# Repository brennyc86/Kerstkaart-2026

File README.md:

# Kerstkaart 2026 – Rudolf het rendier

Een printplaat in de vorm van een rendier (96 × 98 mm) met 42 piepkleine NeoPixels. De ATtiny is het **oog**, het knopje is de **neus**,
de overige onderdelen zijn wimpers en wenkbrauw. Op de voorkant staat de kerstboodschap *Zalig Kerstfeest en een gelukkig 2027*.

| Voorkant | Achterkant |
|---|---|
|  |  |

## Ontwerp

| Onderdeel | Type | LCSC |
|---|---|---|
| 42 × LED | SK6805-EC15, 1,5 × 1,5 mm NeoPixel (5 mA, 3,7–5,5 V) | C2890035 |
| Oog | ATtiny1616-MNR, VQFN-20 3×3 mm | C507118 |
| Neus | Omron B3U-1000P, 3 × 2,5 mm tactknopje | C231329 |
| C1 / R1 / R2 | 100 nF / 330 Ω (data) / 4,7 kΩ (UPDI), alle 0603 | C14663 / C23138 / C23162 |

* **Chip als oog:** een witte silkring maakt van de QFN de pupil; C1, R1 en R2 staan rond de ring als wimpers, met een wenkbrauw erboven.
* **Knop als neus:** de B3U zit in de snuit, met de rode neus-LED ernaast; een silkring om beide. Indrukken = volgend lichtprogramma, lang indrukken = helderheid.
* **Geweien identiek:** gewei A is een exacte spiegel van gewei B (elk 5 LED's); de firmware gebruikt `gewei_rang()` zodat alle effecten links en rechts gelijk lopen.
* **LED's recht:** alle LED's staan in 0°/90°/180°/270° t.o.v. de footprint.
* **Batterij (3 × AAA, ≥ 4,5 V):** grote koperpads `+` / `-` op de achterkant (4,6 × 3,8 mm) om draden of een batterijhouder op te solderen. De JST-connector is vervallen.
* **Programmeren, op de achterkant:** rij `GND – UPDI 4k7 – VCC` met UPDI in het midden (via R2), en een aparte pad **`HV: UPDI direct`** die rechtstreeks aan de UPDI-pen hangt voor hoogspanningsprogrammering.
* **Pinnen** (uit het KiCad-symbool): pen 3 GND, 4 VCC, 8 PA7 = knop, 15 PC0 = data, 19 UPDI, 21 = EP (GND).

* **Koper tot de rand:** beide lagen zijn gevuld tot 0,3 mm van de rand (voorkant GND, achterkant VCC), ook smalle randstroken. Losse stukken zijn zwevend koper, puur optisch.
* **GND-via's:** bij elke GND-aansluiting (alle LED's, ATtiny, C1, knop) zit een via vlak ernaast. De onderlaag is VCC-vlak, dus elke via heeft daar een klein eilandje met vrije ruimte eromheen.

## Kleurkeuze (1 kleur silk)
Zwart soldeermasker, witte silk, ENIG-goud: de LED's lichten het mooist op, de boodschap is goed leesbaar en het goud accentueert de blanke pads (`HV`, `UPDI`, batterijpads, oog en neus).
Alternatief: rood masker + witte silk. Een volledig kleuren-silkscreen is een EasyEDA Pro-functie die ik hier niet kan genereren.

## Bestanden

| Pad | Inhoud |
|---|---|
| `kerstkaart_2026_gerber.zip` | Gerbers + boorbestand (JLCPCB) |
| `productie/BOM_kerstkaart_2026.csv`, `productie/CPL_kerstkaart_2026.csv` | Stuklijst en plaatsingsbestand |
| `kerstkaart2026.kicad_pcb` | KiCad-bord (KiCad 10-formaat, **ongetest**, de Gerbers zijn leidend) |
| `footprints/` | De KiCad-bibliotheekfootprints van alle onderdelen |
| `firmware/kerstkaart2026/` | Arduino-sketch (megaTinyCore + tinyNeoPixel) + `leds.h` |
| `gen.py`, `shape.py`, `ketting.py`, `kunst.py`, `sexp.py` | Generator: silhouet, LED-volgorde, silk-kunst → Gerbers, BOM, CPL, renders, `leds.h` |

## Nog controleren
* **Gerbers/CPL:** ingelezen met `gerbonara` (8 lagen + boorbestand herkend), maar niet in KiCad of in JLC's viewer bekeken. Controleer daar de **rotatie** van LED's, U1, knop en connector (JLC wijkt soms 90°/180° af), en of JLC de SK6805-EC15 en B3U-1000P op voorraad heeft.
* **Mijn eigen controle** (spoor/pad-afstand 0,2 mm, randafstand 0,4 mm, GND en VCC elk één samenhangend vlak) is geen volledige DRC.
* **SK6805-EC15:** pinout uit de datasheet (1 DIN, 2 VDD, 3 DOUT, 4 GND, GND linksboven gezien van boven); de padmaten (0,5 × 0,5 mm op 0,9 mm) komen uit de KiCad EC15-footprint, niet uit de datasheet-afbeelding. Het type is dimmer (5 mA) en heeft minstens 3,7 V nodig: een bijna lege batterij laat de LED's eerder uitvallen dan de chip.
* De 0603-LCSC-nummers zijn niet apart geverifieerd. De 5-LED-geweien laten de binnenste zijtak onverlicht.
* Firmware alleen op syntax gecontroleerd, niet op een echte ATtiny.

## Licentie en bronnen
De footprints in `footprints/` komen uit de KiCad-bibliotheken (CC-BY-SA 4.0 met uitzondering voor het gebruik in ontwerpen). De overige bestanden zijn van Brendan.

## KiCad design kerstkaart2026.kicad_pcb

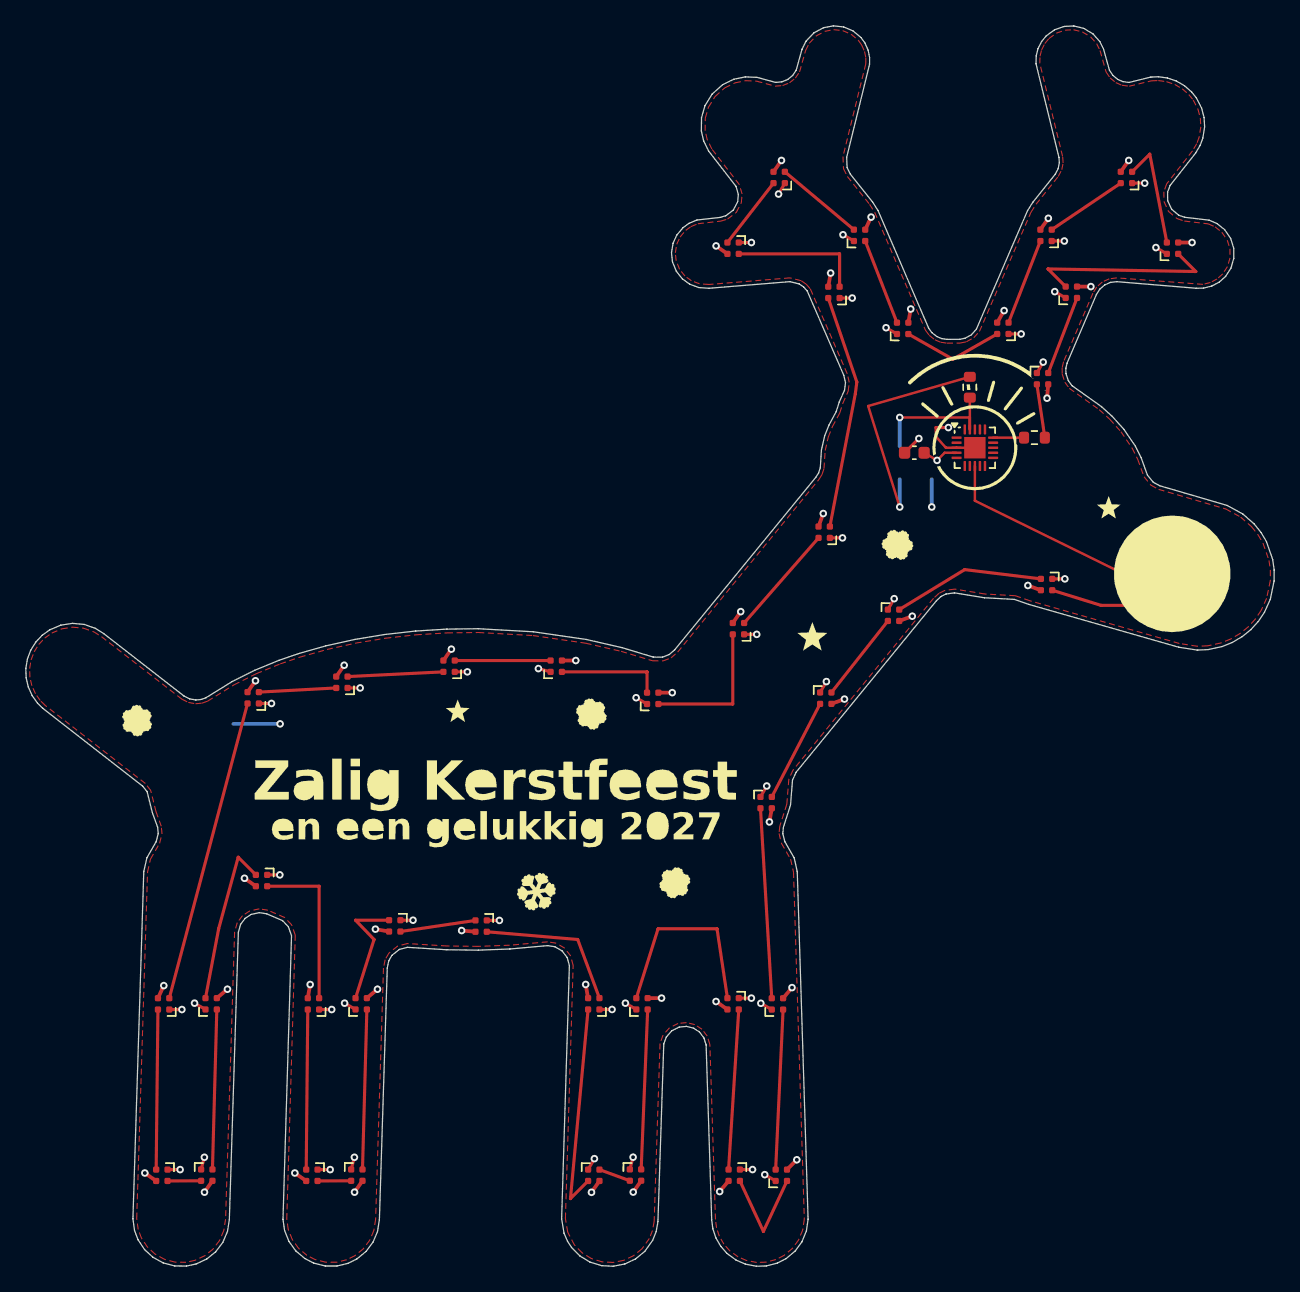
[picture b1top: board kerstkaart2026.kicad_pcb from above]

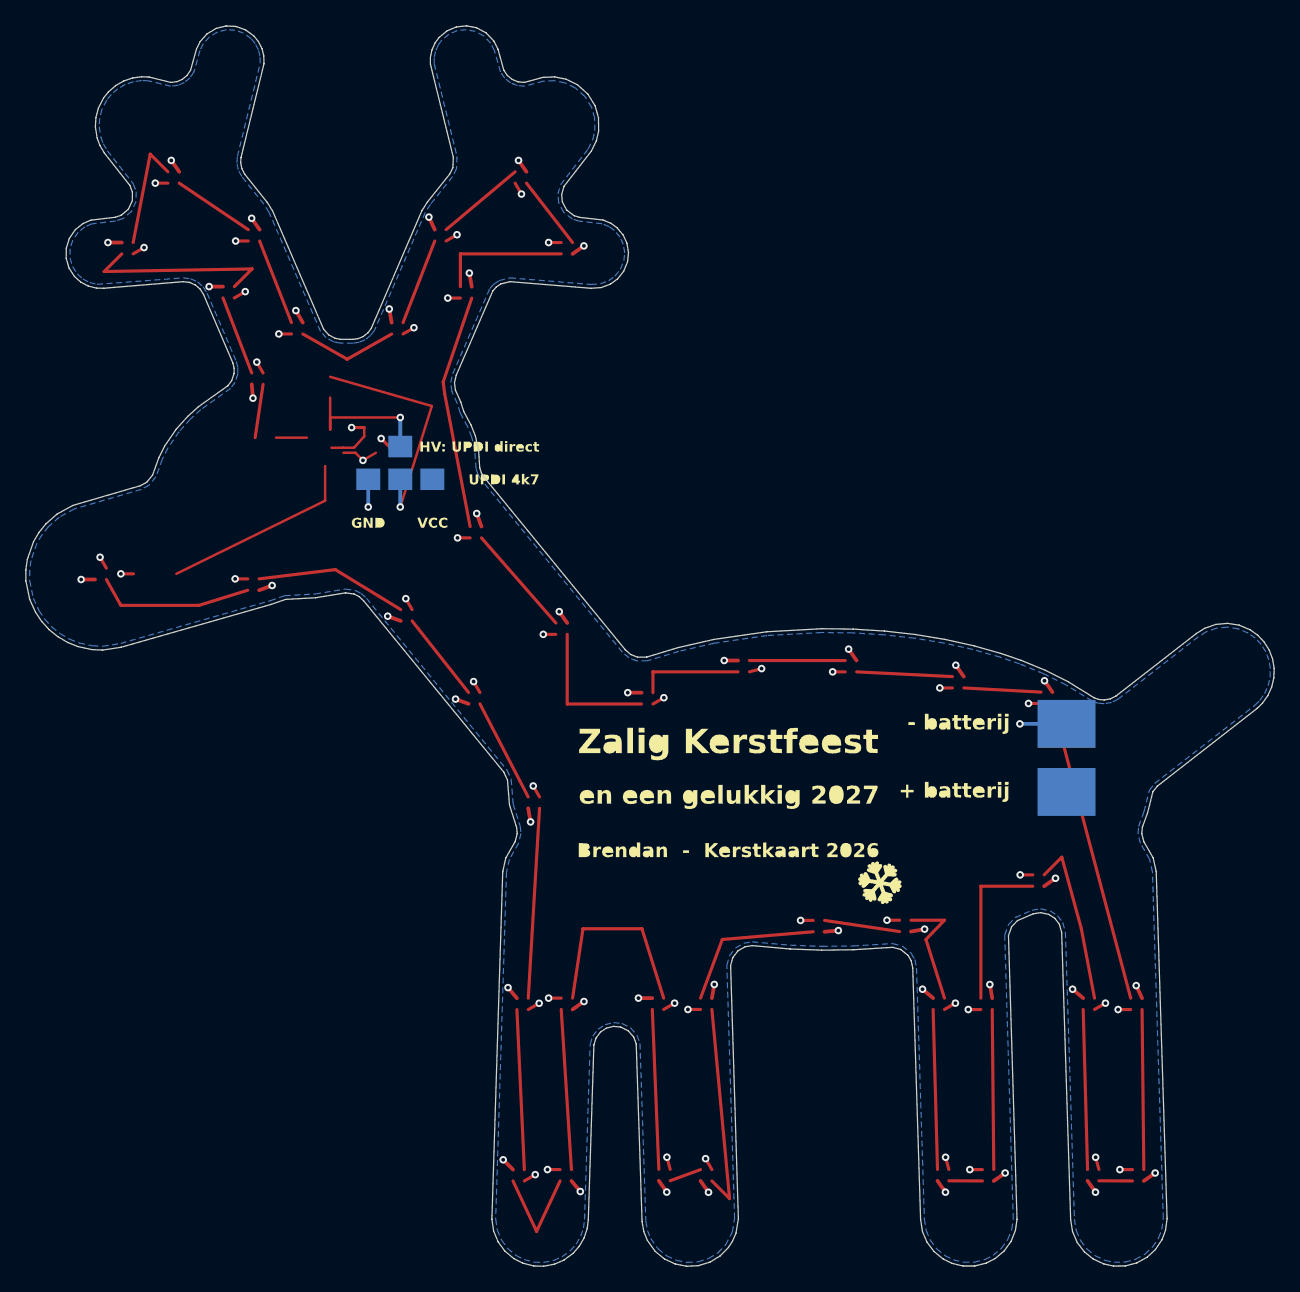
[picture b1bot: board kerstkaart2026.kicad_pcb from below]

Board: 2 copper layers, 99.0 x 98.4 mm, 53 parts (6 on the bottom side), 48 nets.

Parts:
C1: 100nF 0603; C_0603_1608Metric
D1, D2, D3, D4, D5, D6, D7, D8, D9, D10, D11, D12, D13, D14, D15, D16, D17, D18, D19, D20, D21, D22, D23, D24, D25, D26, D27, D28, D29, D30, D31, D32, D33, D34, D35, D36, D37, D38, D39, D40, D41, D42: SK6805-EC15; LED_SK6812_EC15_1.5x1.5mm
R1: 330R 0603; R_0603_1608Metric
R2: 4.7k 0603; R_0603_1608Metric
SW1: B3U-1000P; SW_SPST_B3U-1000P
TP_BT+: Pad_BT+
TP_BT-: Pad_BT-
TP_GND: Pad_GND
TP_HV: Pad_HV
TP_UPDI: Pad_UPDI
TP_VCC: Pad_VCC
U1: ATtiny1616-MNR (VQFN-20); VQFN-20-1EP_3x3mm_P0.4mm_EP1.7x1.7mm

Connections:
BTN: SW1.1, U1.8
D1: D1.3, D2.1
D2: D2.3, D3.1
D3: D3.3, D4.1
D4: D4.3, D5.1
D5: D5.3, D6.1
D6: D6.3, D7.1
D7: D7.3, D8.1
D8: D8.3, D9.1
D9: D9.3, D10.1
D10: D10.3, D11.1
D11: D11.3, D12.1
D12: D12.3, D13.1
D13: D13.3, D14.1
D14: D14.3, D15.1
D15: D15.3, D16.1
D16: D16.3, D17.1
D17: D17.3, D18.1
D18: D18.3, D19.1
D19: D19.3, D20.1
D20: D20.3, D21.1
D21: D21.3, D22.1
D22: D22.3, D23.1
D23: D23.3, D24.1
D24: D24.3, D25.1
D25: D25.3, D26.1
D26: D26.3, D27.1
D27: D27.3, D28.1
D28: D28.3, D29.1
D29: D29.3, D30.1
D30: D30.3, D31.1
D31: D31.3, D32.1
D32: D32.3, D33.1
D33: D33.3, D34.1
D34: D34.3, D35.1
D35: D35.3, D36.1
D36: D36.3, D37.1
D37: D37.3, D38.1
D38: D38.3, D39.1
D39: D39.3, D40.1
D40: D40.3, D41.1
D41: D41.3, D42.1
DATA0: R1.1, U1.15
DATA1: D1.1, R1.2
GND: C1.1, D1.4, D2.4, D3.4, D4.4, D5.4, D6.4, D7.4, D8.4, D9.4, D10.4, D11.4, D12.4, D13.4, D14.4, D15.4, D16.4, D17.4, D18.4, D19.4, D20.4, D21.4, D22.4, D23.4, D24.4, D25.4, D26.4, D27.4, D28.4, D29.4, D30.4, D31.4, D32.4, D33.4, D34.4, D35.4, D36.4, D37.4, D38.4, D39.4, D40.4, D41.4, D42.4, SW1.2, TP_BT-.1, TP_GND.1, U1.3, U1.21
UPDI0: R2.1, TP_HV.1, U1.19
UPDI_R: R2.2, TP_UPDI.1
VCC: C1.2, D1.2, D2.2, D3.2, D4.2, D5.2, D6.2, D7.2, D8.2, D9.2, D10.2, D11.2, D12.2, D13.2, D14.2, D15.2, D16.2, D17.2, D18.2, D19.2, D20.2, D21.2, D22.2, D23.2, D24.2, D25.2, D26.2, D27.2, D28.2, D29.2, D30.2, D31.2, D32.2, D33.2, D34.2, D35.2, D36.2, D37.2, D38.2, D39.2, D40.2, D41.2, D42.2, TP_BT+.1, TP_VCC.1, U1.4

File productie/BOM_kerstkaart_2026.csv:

Comment,Designator,Footprint,LCSC Part #
"ATtiny1616-MNR (VQFN-20)","U1",VQFN-20-1EP_3x3mm_P0.4mm_EP1.7x1.7mm,C507118
"100nF 0603","C1",C_0603_1608Metric,C14663
"330R 0603","R1",R_0603_1608Metric,C23138
"4.7k 0603","R2",R_0603_1608Metric,C23162
"B3U-1000P","SW1",SW_SPST_B3U-1000P,C231329
"SK6805-EC15","D1,D2,D3,D4,D5,D6,D7,D8,D9,D10,D11,D12,D13,D14,D15,D16,D17,D18,D19,D20,D21,D22,D23,D24,D25,D26,D27,D28,D29,D30,D31,D32,D33,D34,D35,D36,D37,D38,D39,D40,D41,D42",LED_SK6812_EC15_1.5x1.5mm,C2890035
